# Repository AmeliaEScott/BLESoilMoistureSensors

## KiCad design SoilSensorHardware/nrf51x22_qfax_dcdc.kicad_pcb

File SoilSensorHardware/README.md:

Nordic provides reference designs for Altium only. This is the nRF52832-QFAA_Ref_Layout_v0.9.zip reference layout

Ideally you could use altium's free www.circuitmaker.com to view the paid Circuit Designer files, but thats not the case unless they have already previously been exported as an autocad file:
https://www.youtube.com/watch?v=YAWBsShCId4

As thats not the case for these Nordic files I decided to play.

In the end I finally found a 'free' viewer (for 6 months) from Altium that is really all you need to get a look at the design decisions.
http://www.altium.com/altium-designer-viewer 

However I wanted to play with kicad and https://github.com/thesourcerer8/altium2kicad to see how close it gets

Fixed issues:
* Schematic wouldnt come over for some reason, I had to build that by hand.
* The Polygons didn't come in quite right, I made them Thermal Releif's and Polygons and that seemed to help.
* Keepout Polys were lost and recreated by hand
* Stiching Vias are.. problematic, in kicad so those needed to be handled by hand https://forum.kicad.info/t/protip-nicer-via-stitching/1103/32
* File-Archive Footprints->Create library Exported the footprints out of the design into a proper library, and moved the .3dshapes locally as well

Known issues:
* Altium has the no poly islands smaller than xsq but kicad doesnt appear to which means a few little islands exist on our gerbers that dont on theirs.

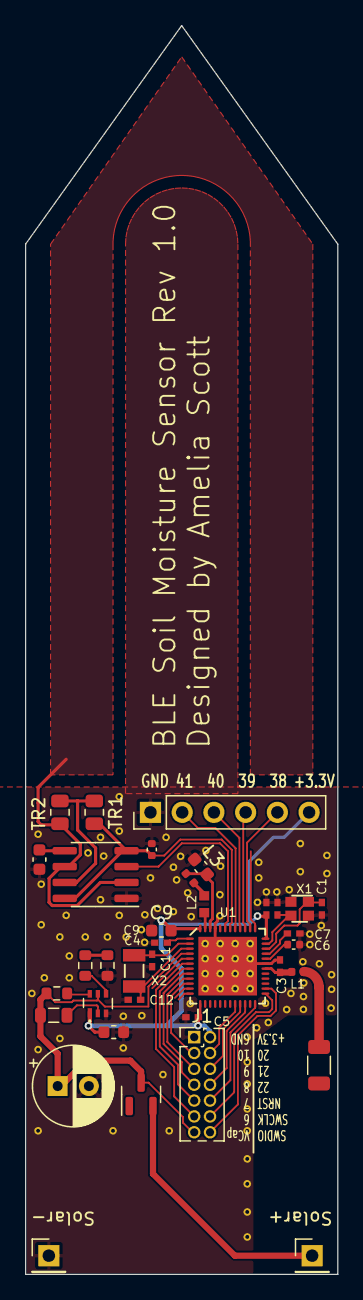
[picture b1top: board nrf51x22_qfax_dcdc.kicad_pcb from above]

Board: 2 copper layers, 25.0 x 100.0 mm, 36 parts (0 on the bottom side), 40 nets.

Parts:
AE1: Antenna_Chip; R_1206_3216Metric
BigBoi1: 1; CP_Radial_D6.3mm_P2.50mm
C1, C2, C11, C12: 12pF; CAPC1005X04L
C3: .8pF; CAPC1005X04L
C4, C5, C8: 100nF; CAPC1005X04L
C6: NC; C_0402_1005Metric
C7: 100pF; CAPC1005X04L
C9: 4.7uF; C_0603_1608Metric
C10: 1.0uF; C_0603_1608Metric
C13: 10u; L_0603_1608Metric
C14: 100n; C_0402_1005Metric
D1: BAT54C,215; SOT-23
DCDC1: MAX17220ELT+T; MAX17220ELT&plus_T
J1: Conn_02x07_Odd_Even; PinHeader_2x07_P1.27mm_Vertical
J2: Conn_01x06; PinHeader_1x06_P2.54mm_Vertical
L1: 3.9nH; L_0402_1005Metric
L2: 10uH; INDC1608X06L
L3: 15nH; L_0402_1005Metric
L4: 2.2u; L_0805_2012Metric
R1: 75k; R_0603_1608Metric
R2: 5.6k; R_0603_1608Metric
R3: 33M; R_0603_1608Metric
Solar+1: Conn_01x01; PinHeader_1x01_P2.54mm_Vertical
Solar-1: Conn_01x01; PinHeader_1x01_P2.54mm_Vertical
TC1: 10n; C_0603_1608Metric
TR1: 1k; R_0805_2012Metric
TR2: 10k; R_0805_2012Metric
U1: nrf52810-QFAA-T; nrf51-qfax-1ep-vias
U2: TLC555xD; SOIC-8_3.9x4.9mm_P1.27mm
X1: Crystal-4; BT-XTAL_2016
X2: 32.768kHz; XTAL_3215

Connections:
+3.3v: C5.2, C8.2, C9.2, C13.2, DCDC1.1 (OUT), J1.2, J2.6, U1.13 (VDD), U1.36 (VDD), U1.48 (VDD)
/Probe: TR2.2, U2.2 (TR), U2.6 (THR)
DB5: J1.5, U1.9 (P0.07)
DB7: J1.7, U1.8 (P0.06)
DB9: J1.9, U1.7 (P0.05/AIN3)
DB11: J1.11, U1.6 (P0.04/AIN2)
GND: BigBoi1.2, C1.2, C2.2, C3.2, C4.1, C5.1, C6.1, C7.1, C8.1, C9.1, C10.1, C11.1, C12.1, C13.1, C14.2, DCDC1.3 (GND), J1.1, J2.1, R2.2, Solar-1.1, TC1.2, U1.31 (VSS), U1.45 (VSS), U1.49 (THERMAL), U2.1 (GND), X1.2 (4), X1.4
NRST: J1.10, U1.24 (P0.21/RESET)
unnamed: C1.1, U1.34 (XC1), X1.1
unnamed: C2.1, U1.35 (XC2), X1.3
unnamed: C3.1, L1.1, U1.30 (ANT)
unnamed: C4.2, U1.1 (DEC1)
unnamed: C6.2, U1.32 (DEC2)
unnamed: C7.2, U1.33 (DEC3)
unnamed: C10.2, L3.1, U1.46 (DEC4)
unnamed: C11.2, U1.2 (P0.00/XL1), X2.2
unnamed: C12.2, U1.3 (P0.01/XL2), X2.1
unnamed: D1.2 (A), Solar+1.1
unnamed: DCDC1.2 (LX), L4.1
unnamed: DCDC1.4 (SEL), R1.1
unnamed: DCDC1.6 (EN), R3.1
unnamed: J1.3, U1.10 (P0.08)
unnamed: J1.4, U1.20 (P0.17)
unnamed: J1.6, U1.21 (P0.18)
unnamed: J1.8, U1.22 (P0.19)
unnamed: J2.2, U1.41 (P0.29/AIN5)
unnamed: J2.3, U1.40 (P0.28/AIN4)
unnamed: J2.4, U1.39 (P0.27)
unnamed: J2.5, U1.38 (P0.26)
unnamed: AE1.1 (FEED), L1.2
unnamed: L2.1, L3.2
unnamed: L2.2, U1.47 (DCC)
unnamed: R1.2, R2.1
unnamed: TC1.1, U2.5 (CV)
unnamed: TR1.2, TR2.1, U2.7 (DIS)
Probe Timer Output: U1.43 (P0.31/AIN7), U2.3 (Q)
Probe Timer Power: C14.1, TR1.1, U1.42 (P0.30/AIN6), U2.4 (R), U2.8 (VCC)
SWCLK: J1.12, U1.25 (SWDCLK)
SWDIO: J1.14, U1.26 (SWDIO)
VCap: BigBoi1.1, D1.3 (K), DCDC1.5 (IN), J1.13, L4.2, R3.2, U1.4 (P0.02/AIN0)

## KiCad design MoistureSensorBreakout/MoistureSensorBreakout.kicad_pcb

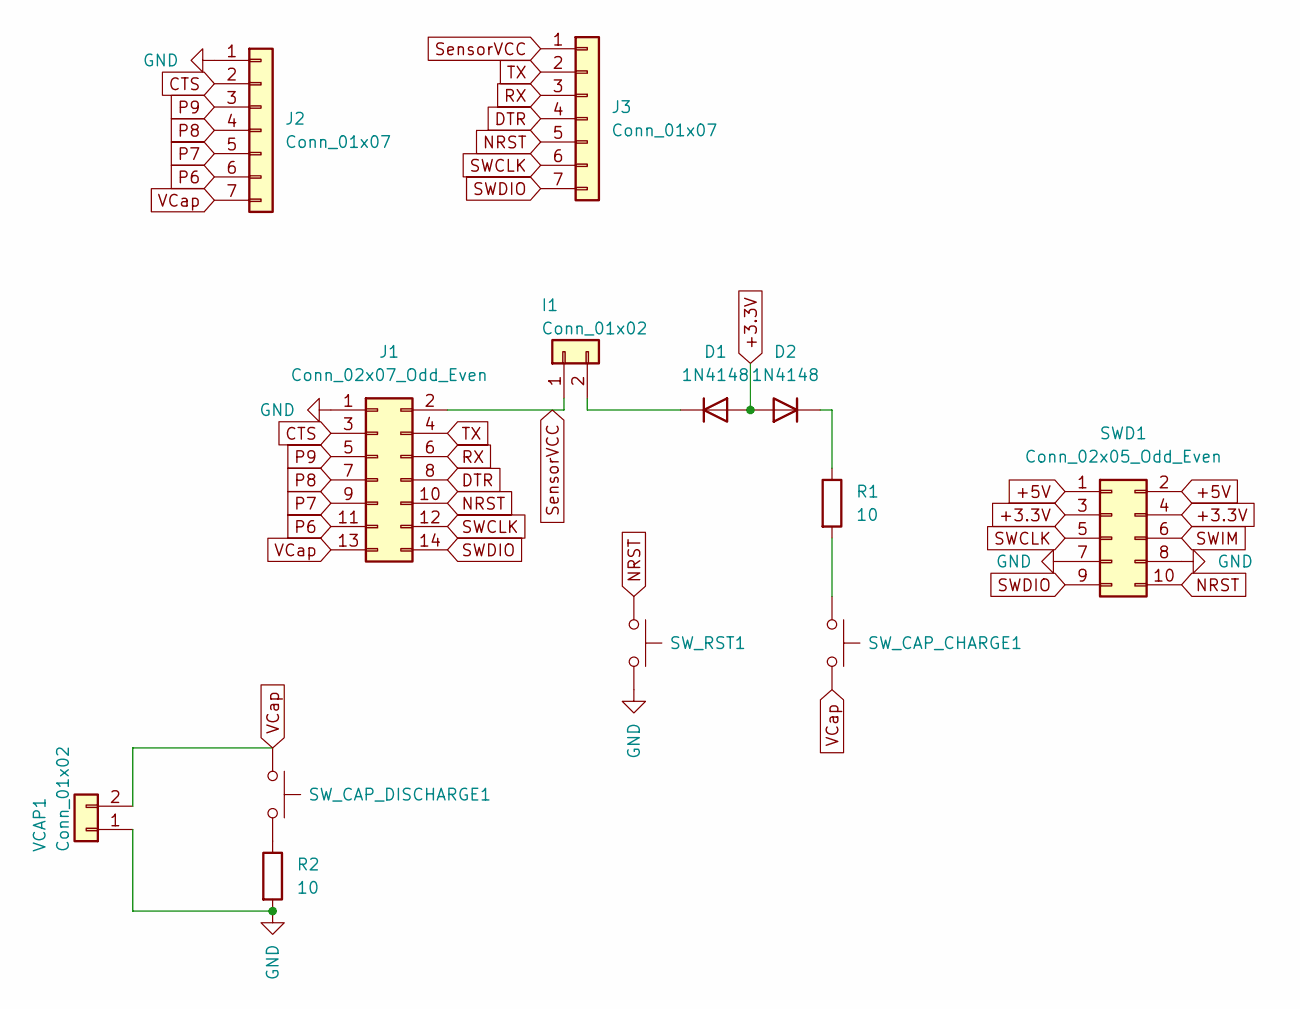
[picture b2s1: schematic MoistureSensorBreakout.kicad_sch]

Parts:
D1, D2: 1N4148; D_DO-35_SOD27_P7.62mm_Horizontal
I1: Conn_01x02; PinHeader_1x02_P2.54mm_Vertical
J1: Conn_02x07_Odd_Even; PinHeader_2x07_P1.27mm_Vertical
J2, J3: Conn_01x07; PinHeader_1x07_P2.54mm_Vertical
R1, R2: 10; R_Axial_DIN0207_L6.3mm_D2.5mm_P7.62mm_Horizontal
SWD1: Conn_02x05_Odd_Even; PinHeader_2x05_P2.54mm_Horizontal
SW_CAP_CHARGE1: SW_Push; SW_PUSH_6mm
SW_CAP_DISCHARGE1: SW_Push; SW_PUSH_6mm
SW_RST1: SW_Push; SW_PUSH_6mm
VCAP1: Conn_01x02; PinHeader_1x02_P2.54mm_Vertical

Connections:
+3.3V: D1.2 (A), D2.2 (A), SWD1.3, SWD1.4
+5V: SWD1.1, SWD1.2
CTS: J1.3, J2.2
DTR: J1.8, J3.4
GND: J1.1, J2.1, R2.2, SWD1.7, SWD1.8, SW_RST1.2, VCAP1.1; also elsewhere on the board
NRST: J1.10, J3.5, SWD1.10, SW_RST1.1
unnamed: D1.1 (K), I1.2
unnamed: D2.1 (K), R1.1
unnamed: R1.2, SW_CAP_CHARGE1.1
unnamed: R2.1, SW_CAP_DISCHARGE1.2
P6: J1.11, J2.6
P7: J1.9, J2.5
P8: J1.7, J2.4
P9: J1.5, J2.3
RX: J1.6, J3.3
SWCLK: J1.12, J3.6, SWD1.5
SWDIO: J1.14, J3.7, SWD1.9
SWIM: SWD1.6
SensorVCC: I1.1, J1.2, J3.1
TX: J1.4, J3.2
VCap: J1.13, J2.7, SW_CAP_CHARGE1.2, SW_CAP_DISCHARGE1.1, VCAP1.2; also elsewhere on the board

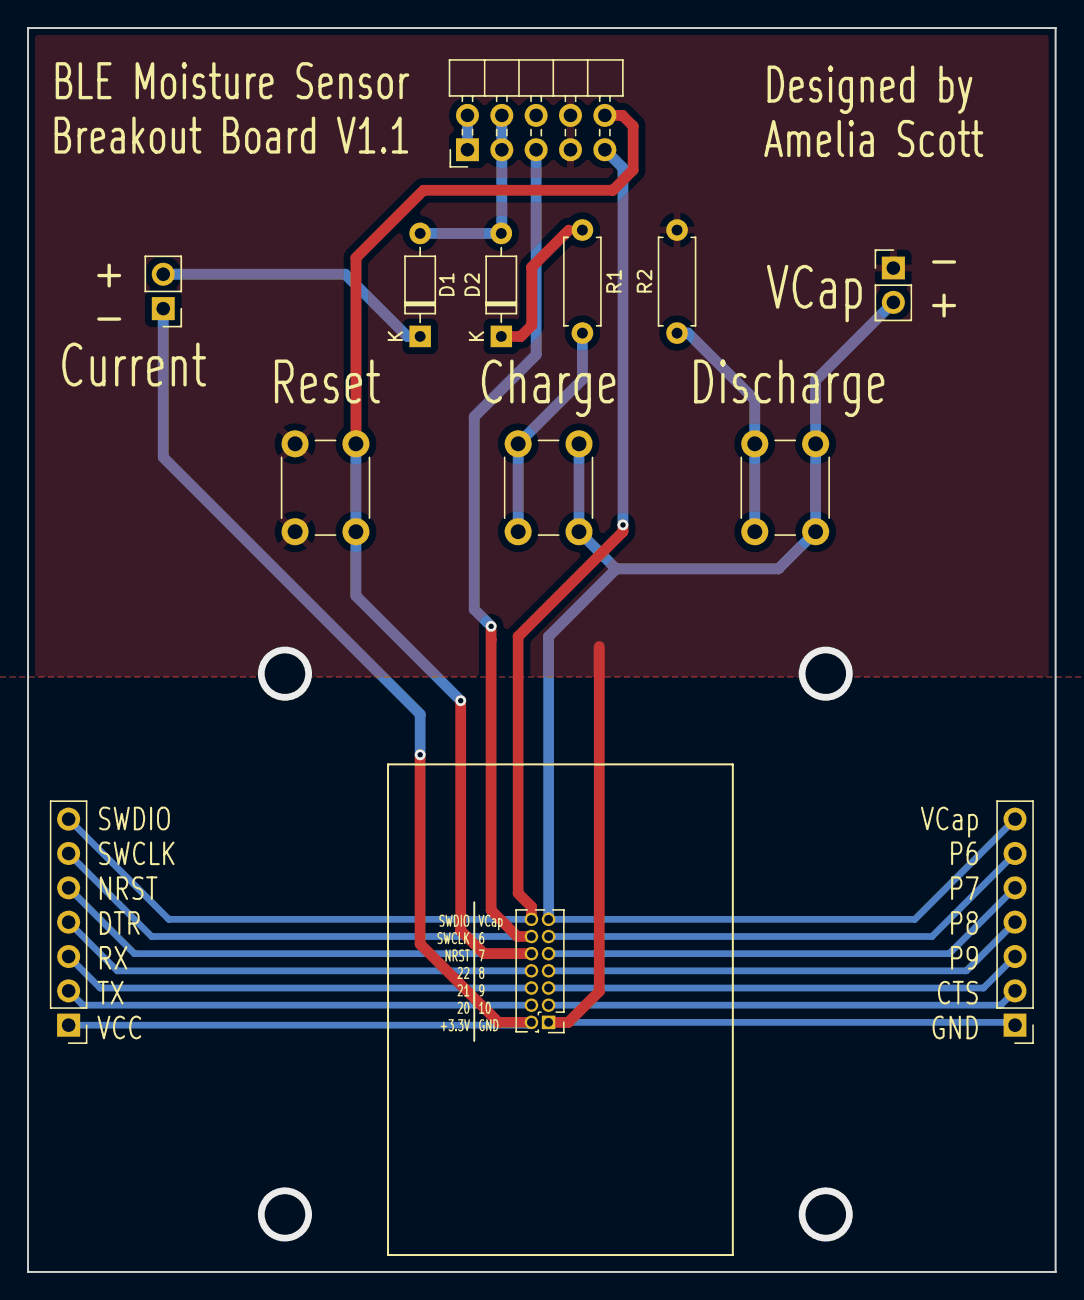
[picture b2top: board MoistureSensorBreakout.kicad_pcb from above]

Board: 2 copper layers, 76.0 x 92.0 mm, 13 parts (0 on the bottom side), 20 nets.

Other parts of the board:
VCAP: Conn_01x02; PinHeader_1x02_P2.54mm_Vertical

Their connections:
GND: VCAP.1; also elsewhere on the board
VCap: VCAP.2; also elsewhere on the board

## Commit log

2023-06-02 Basic example which compiles. Does it work??? We'll see!
2023-06-03 RTC now works, along with Defmt
2023-06-03 Added README
2023-06-04 Softdevice working with RTIC
2023-06-04 Fixed (my understanding of) the external low-frequency oscillator
2023-06-06 Added breakout board PCB design
2023-06-07 Capacitance probe timer working
2023-06-08 Reorganization
2023-06-08 Fixed (I think?) timer
2023-06-09 ADC is now working
2023-06-09 Ignore backup zips
2023-06-14 Sorted out bluetooth power management
2023-06-14 serde of Measurement
2023-06-15 Full state machine is now functioning
2023-06-15 Cleanup and squashing warnings
2023-06-15 Compile-time configuration of sensor ID
2023-06-15 Created workspace
2023-06-15 Stop using temperature sensor! It's used by the Softdevice
2023-06-15 Un-workspace
2023-06-15 Fixed interrupt priority
2023-06-16 Re-enabled temperature sensor. Will this break everything? Perhaps!
2023-06-17 Tweaked bluetooth for easier development of BLE bridge
2023-06-17 Minimum demo of BLE bridge
2023-06-17 Reconnect after disconnect
2023-06-18 Trying to manage power draw
2023-06-18 Error handling and more reliable reconnecting
2023-06-26 Created minimum example
2023-07-01 Friendship ended with Softdevice. Now bare metal is my best friend
2023-07-01 Notes for making a more useful breakout board
2023-07-01 New version of breakout / programming board
2023-07-07 Uhhhhhhh
2023-07-07 Enable reset pin
2023-07-07 It wasn't this
2023-07-07 Floating reset pin = bad idea
2023-07-08 Attempting to address errata
2023-07-08 Errata? I 'ardly know 'uh!
2023-07-08 Updated schematic
2023-07-08 Added breakout board schematic
2023-07-12 Moved power trace from under HF crystal
2023-07-12 Basic functionality of beacon mode
2023-07-20 Now using BlueR directly to listen for manufacturer data
2023-07-20 Friendship ended with monotonics. Now low power usage is my best friend
2023-07-21 Updated the firmware
2023-07-21 A better BLE bridge
2023-07-21 Cleanup, cleanup, everybody cleanup!
2023-08-05 Fixed sleep duration
2023-08-05 I don't even remember what I changed here
2023-08-05 Added server Cargo project
2023-08-05 Diesel demo
2023-08-12 I am learning how to use Diesel
2024-02-20 Reminding myself how Diesel works
2024-10-02 Updates to make it build and run onece more
2024-10-02 Influx time!
2024-10-03 I don't remember what's in these changes. Just committing so I have it in case it ends up being important
2024-10-03 Friendship ended with custom server. Now InfluxDB is my best friend

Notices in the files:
parts and their libraries:
Copyright 2021 Accelerated Designs. All rights reserved.
